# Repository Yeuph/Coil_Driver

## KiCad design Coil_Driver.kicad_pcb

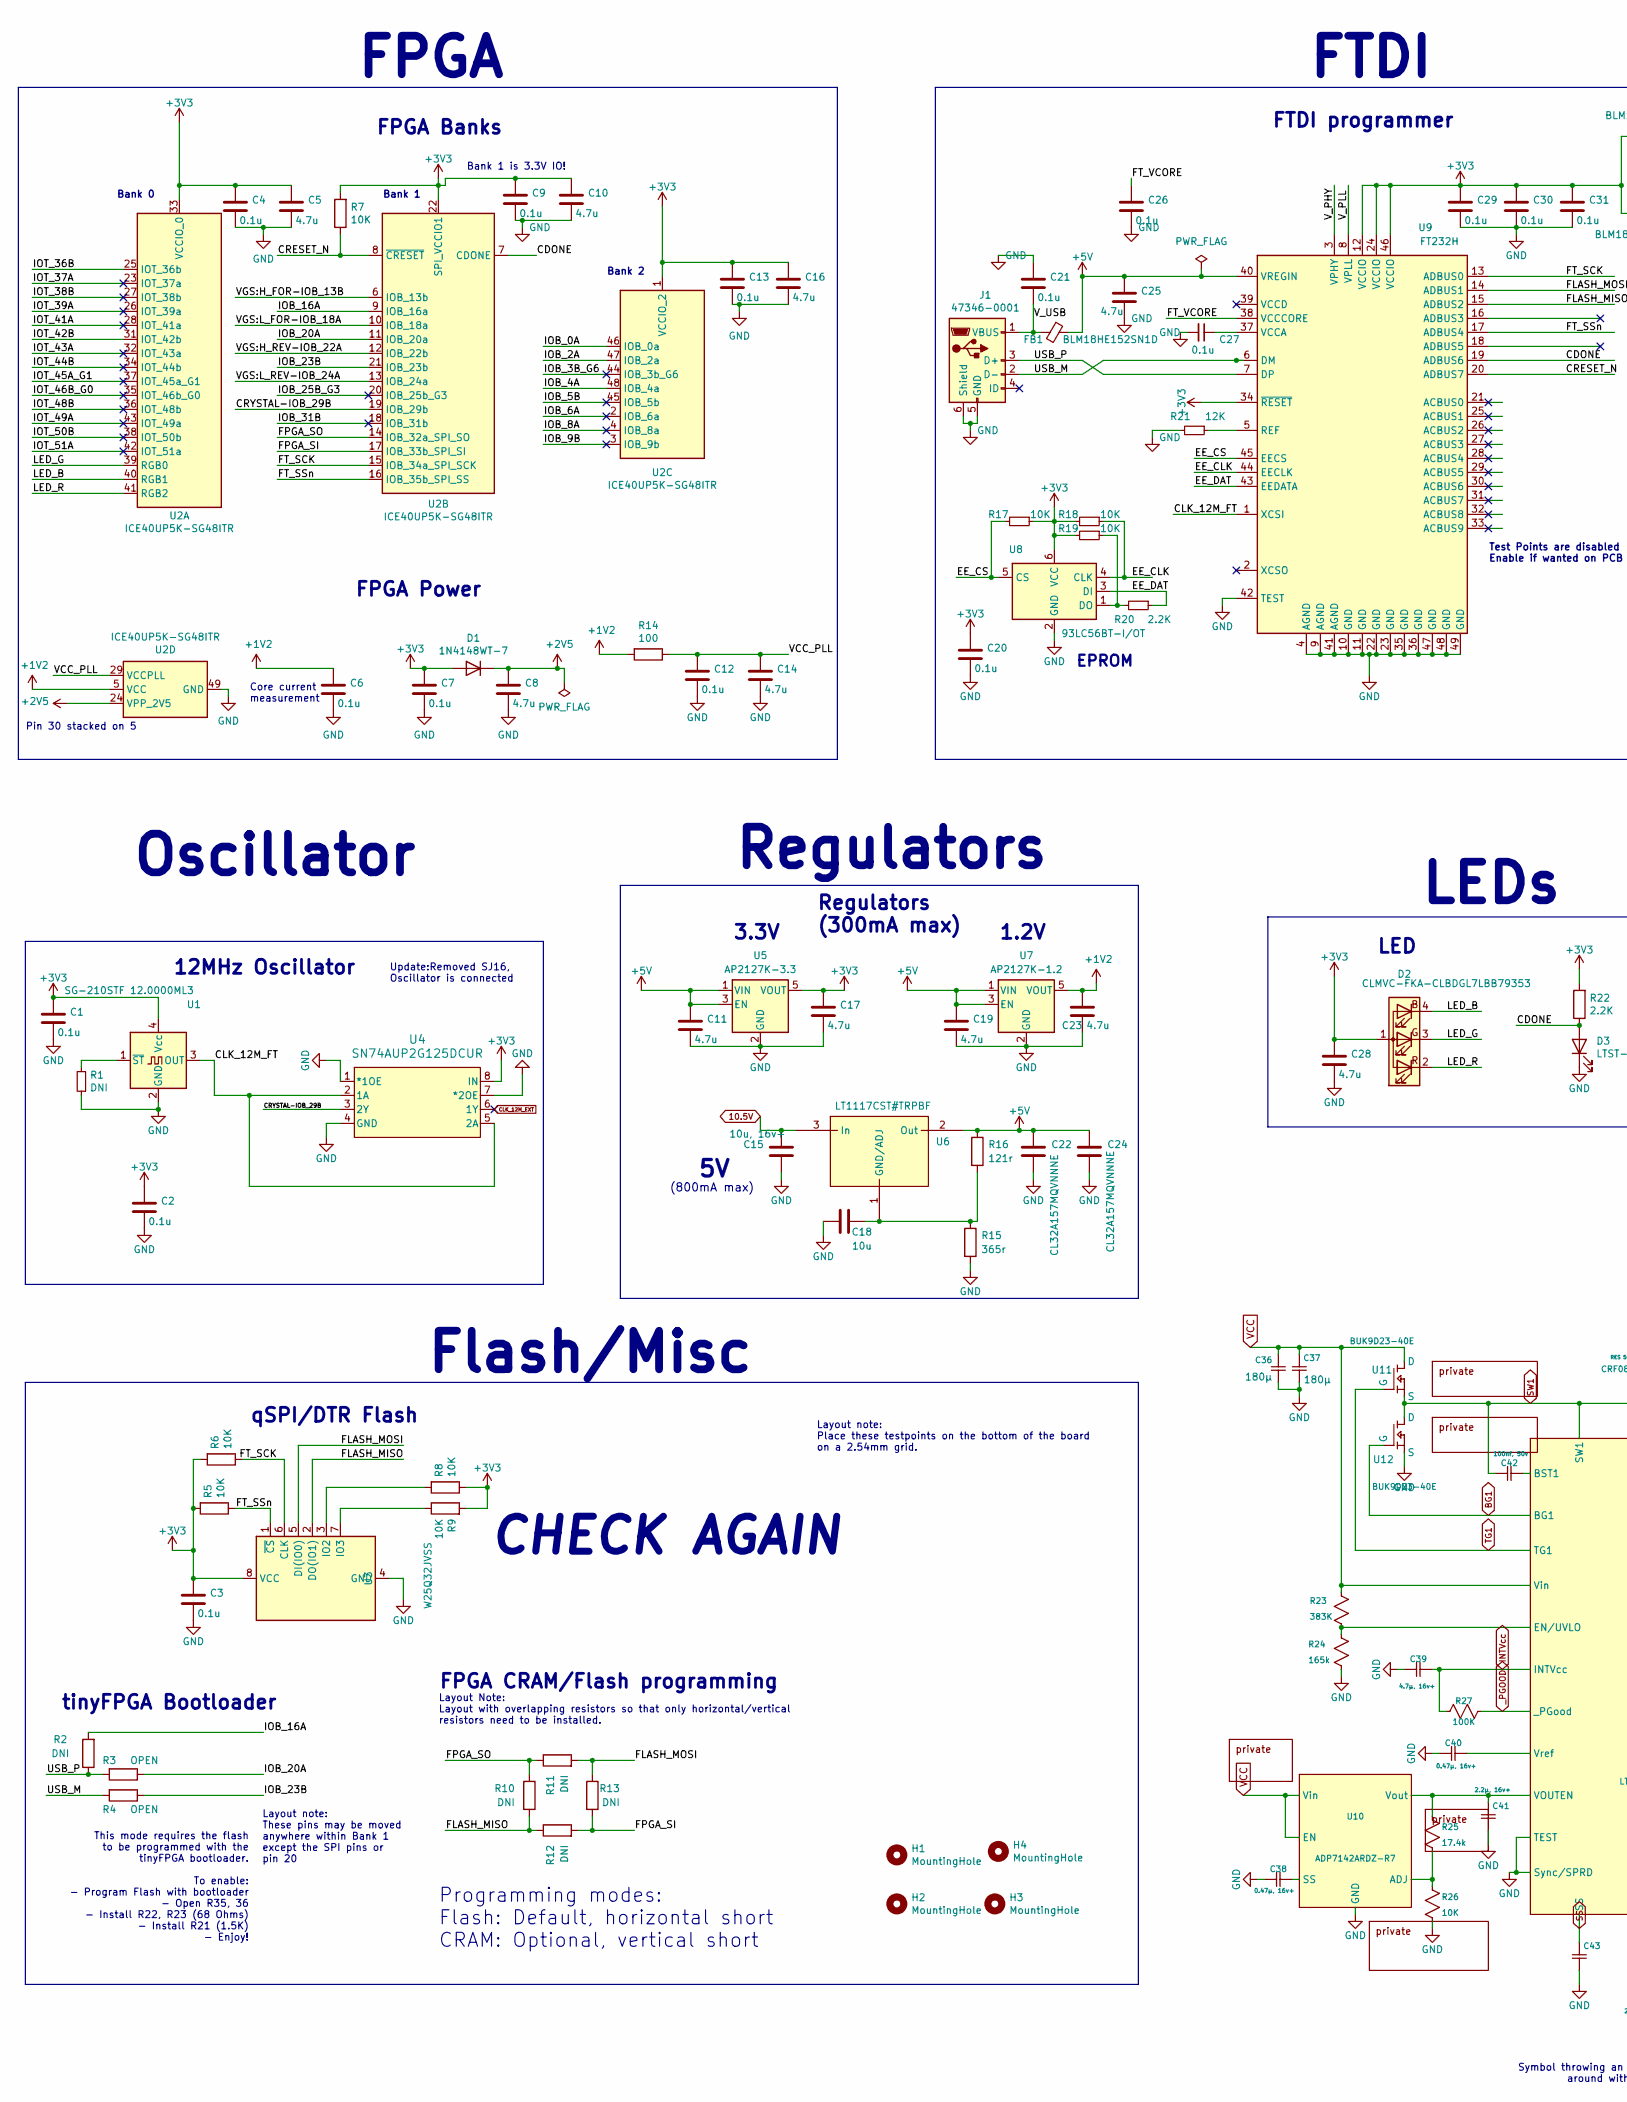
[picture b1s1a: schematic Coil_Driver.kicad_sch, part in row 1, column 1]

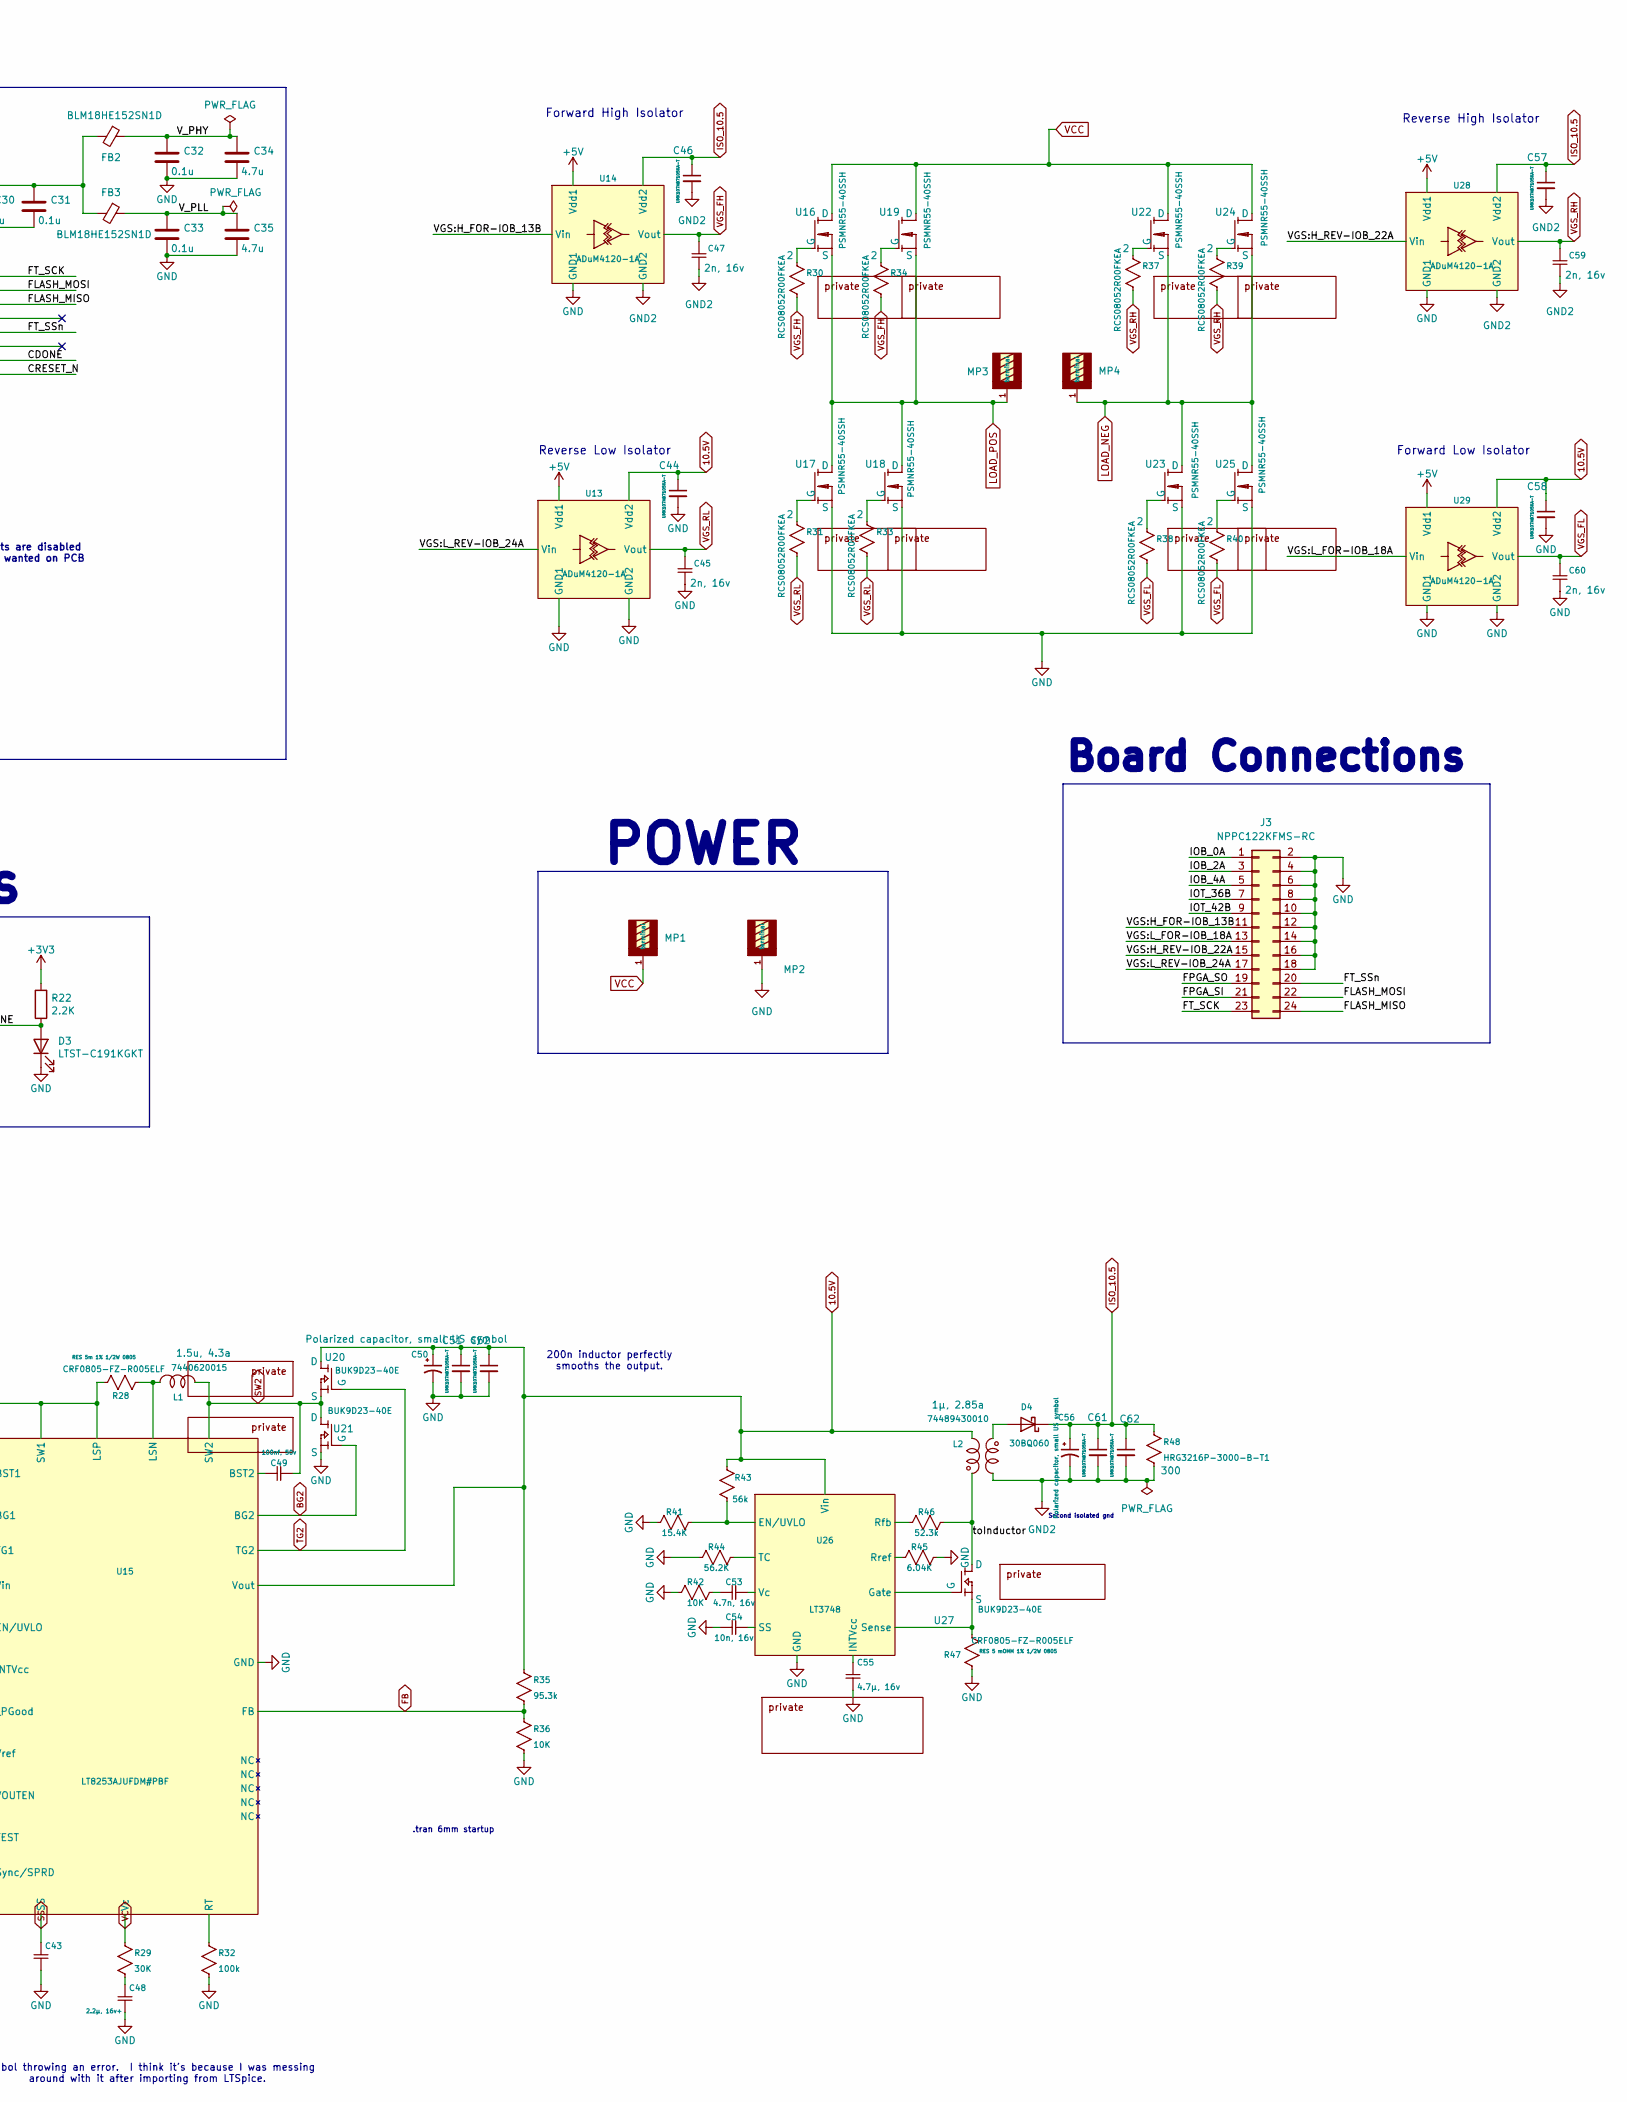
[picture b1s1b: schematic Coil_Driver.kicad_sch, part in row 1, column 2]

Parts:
C1, C2, C3, C6, C7, C9, C12, C13, C20, C21, C26, C27, C29, C30, C31, C32, C33: 0.1u; C_0603_1608Metric
C4: 0.1u; C_0603_1608Metric; MPN C1005X5R0J104K050BA
C5, C8, C10, C11, C14, C16, C17, C19, C23, C25, C28, C34, C35: 4.7u; C_0603_1608Metric
C15: 10u, 16v+; C_0805_2012Metric
C18: 10u; C_0805_2012Metric
C22, C24: CL32A157MQVNNNE; C_1210_3225Metric
C36, C37: PCR1H181MCL1GS
C38, C40: EMK105ABJ474KV-F; C_0402_1005Metric
C39: CL10A475KO8NNNC; C_0603_1608Metric
C41, C48: CL10A225KO8NNNC; C_0603_1608Metric
C42, C49: CL10B104KB8NNNC; C_0603_1608Metric
C43: GRM155R71C103KA01D; C_0603_1608Metric
C44, C46, C51, C52, C57, C58, C61, C62: UMK107AB7105KA-T; C_0603_1608Metric
C45, C47, C59, C60: C0402C202J3GACTU; C_0402_1005Metric
C50, C56: APXG250ARA221MJA0G
C53: 4.7n, 16v; C_0603_1608Metric
C54: 10n, 16v; C_0603_1608Metric
C55: 4.7µ, 16v; C_0603_1608Metric
D1: 1N4148WT-7; D_SOD-123
D2: CLMVC-FKA-CLBDGL7LBB79353; LED_Cree-PLCC4_2x2mm_CW
D3: LTST-C191KGKT; LED_0603_1608Metric
D4: 30BQ060; D_SMC
FB1, FB2, FB3: BLM18HE152SN1D; L_0603_1608Metric
H1, H2, H3, H4: MountingHole; MountingHole_3.2mm_M3
J1: 47346-0001; USB_Micro-B_Molex_47346-0001
J3: NPPC122KFMS-RC; PinHeader_2x12_P2.54mm_Vertical_SMD
L1: 7440620015; WE-TPC_6823
L2: 74489430010; WE-TDC-8018
MP1, MP2, MP3, MP4: 7466205R; PART-NUMBER 7466205R
R1, R2, R10, R11, R12, R13: DNI; R_0603_1608Metric
R3, R4: OPEN; SolderJumper-2_P1.3mm_Open_TrianglePad1.0x1.5mm
R5, R6, R7, R8, R9, R17, R18, R19, R26: 10K; R_0603_1608Metric
R14: 100; R_0603_1608Metric
R15: 365r; R_0603_1608Metric
R16: 121r; R_0603_1608Metric
R20, R22: 2.2K; R_0603_1608Metric
R21: 12K; R_0603_1608Metric
R23: 383K; R_0603_1608Metric
R24: 165k; R_0603_1608Metric
R25: 17.4k; R_0603_1608Metric
R27: 100K; R_0603_1608Metric
R28, R47: CRF0805-FZ-R005ELF; R_0805_2012Metric
R29: 30K; R_0603_1608Metric
R30, R31, R33, R34, R37, R38, R39, R40: RCS08052R00FKEA; R_0805_2012Metric
R32: 100k; R_0603_1608Metric
R35: 95.3k; R_0402_1005Metric
R36, R42: 10K; R_0402_1005Metric
R41: 15.4K; R_0402_1005Metric
R43: 56k; R_0402_1005Metric
R44: 56.2K; R_0402_1005Metric
R45: 6.04K; R_0402_1005Metric
R46: 52.3k; R_0402_1005Metric
R48: HRG3216P-3000-B-T1; R_1206_3216Metric
U1: SG-210STF 12.0000ML3; Oscillator_SMD_SeikoEpson_SG210-4Pin_2.5x2.0mm
U2: ICE40UP5K-SG48ITR; QFN-48-1EP_7x7mm_P0.5mm_EP5.6x5.6mm
U3: W25Q32JVSS; SOIC-8_5.23x5.23mm_P1.27mm
U4: SN74AUP2G125DCUR; VSSOP-8_2.3x2mm_P0.5mm
U5: AP2127K-3.3; SOT-23-5
U6: LT1117CST#TRPBF; SOT-223-3_TabPin2
U7: AP2127K-1.2; SOT-23-5
U8: 93LC56BT-I/OT; SOT-23-6
U9: FT232H; QFN-48-1EP_8x8mm_P0.5mm_EP6.2x6.2mm
U10: ADP7142ARDZ-R7; SOIC-8-1EP_3.9x4.9mm_P1.27mm_EP2.29x3mm
U11, U12, U20, U21, U27: BUK9D23-40E; Diodes_UDFN2020-6_Type-F
U13, U14, U28, U29: ADuM4120-1A; RI_6_1_ADI-M
U15: LT8253AJUFDM#PBF; QFN-28-1EP_4x5mm_P0.5mm_EP2.65x3.65mm
U16, U17, U18, U19, U22, U23, U24, U25: PSMNR55-40SSH; LFPAK88_SOT1235_NEX-M
U26: LT3748; MSOP-12-16_3x4mm_P0.5mm

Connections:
10.5V: C15.1, C44.1, C50.1, C51.1, C52.1, C58.1, L2.2, R35.1, R43.2, U6.3 (In), U13.6 (Vdd2), U15.21 (Vout), U20.1 (D), U20.2 (D), U20.5 (D), U20.6 (D), U20.7 (D), U26.1 (Vin), U29.6 (Vdd2)
+1V2: C6.1, C23.1, R14.2, U2.5 (VCC), U2.30 (VCC), U7.5 (VOUT)
+2V5: C8.1, D1.1 (K), U2.24 (VPP_2V5)
+3V3: C1.1, C2.1, C3.1, C4.1, C5.1, C7.1, C9.1, C10.1, C13.1, C16.1, C17.1, C20.1, C28.1, C29.1, C30.1, C31.1, D1.2 (A), D2.1 (A), FB2.2, FB3.2, R5.2, R6.2, R7.2, R8.1, R9.2, R17.1, R18.2, R19.2, R22.2, U1.4 (Vcc), U2.1 (VCCIO_2), U2.22 (SPI_VCCIO1), U2.33 (VCCIO_0), U3.8 (VCC), U4.8 (IN), U5.5 (VOUT), U8.6 (VCC), U9.12 (VCCIO), U9.24 (VCCIO), U9.34 (~RESET), U9.46 (VCCIO)
+5V: C11.1, C19.1, C22.1, C24.1, C25.1, FB1.1, R16.1, U5.1 (VIN), U5.3 (EN), U6.2 (Out), U7.1 (VIN), U7.3 (EN), U9.40 (VREGIN), U13.1 (Vdd1), U14.1 (Vdd1), U28.1 (Vdd1), U29.1 (Vdd1)
/CDONE: D3.2 (A), R22.1, U2.7 (CDONE), U9.19 (ADBUS6)
/CLK_12M_FT: U1.3 (OUT), U4.2 (1A), U4.5 (2A), U9.1 (XCSI)
/CRESET_N: R7.1, U2.8 (~CRESET), U9.20 (ADBUS7)
/CRYSTAL-IOB_29B: U2.19 (IOB_29b), U4.3 (2Y)
/EE_CLK: R18.1, U8.4 (CLK), U9.44 (EECLK)
/EE_CS: R17.2, U8.5 (CS), U9.45 (EECS)
/EE_DAT: R20.1, U8.3 (DI), U9.43 (EEDATA)
/FLASH_MISO: J3.24, R10.2, R12.1, U3.2 (DO(IO1)), U9.15 (ADBUS2)
/FLASH_MOSI: J3.22, R11.2, R13.1, U3.5 (DI(IO0)), U9.14 (ADBUS1)
/FPGA_SI: J3.21, R12.2, R13.2, U2.17 (IOB_33b_SPI_SI)
/FPGA_SO: J3.19, R10.1, R11.1, U2.14 (IOB_32a_SPI_SO)
/FT_SCK: J3.23, R6.1, U2.15 (IOB_34a_SPI_SCK), U3.6 (CLK), U9.13 (ADBUS0)
/FT_SSn: J3.20, R5.1, U2.16 (IOB_35b_SPI_SS), U3.1 (~CS), U9.17 (ADBUS4)
/FT_VCORE: C26.1, U9.38 (VCCCORE)
/IOB_0A: J3.1, U2.46 (IOB_0a)
/IOB_2A: J3.3, U2.47 (IOB_2a)
/IOB_3B_G6: U2.44 (IOB_3b_G6)
/IOB_4A: J3.5, U2.48 (IOB_4a)
/IOB_5B: U2.45 (IOB_5b)
/IOB_6A: U2.2 (IOB_6a)
/IOB_8A: U2.4 (IOB_8a)
/IOB_9B: U2.3 (IOB_9b)
/IOB_16A: R2.2, U2.9 (IOB_16a)
/IOB_20A: R3.1, U2.11 (IOB_20a)
/IOB_23B: R4.1, U2.21 (IOB_23b)
/IOB_25B_G3: U2.20 (IOB_25b_G3)
/IOB_31B: U2.18 (IOB_31b)
/IOT_36B: J3.7, U2.25 (IOT_36b)
/IOT_37A: U2.23 (IOT_37a)
/IOT_38B: U2.27 (IOT_38b)
/IOT_39A: U2.26 (IOT_39a)
/IOT_41A: U2.28 (IOT_41a)
/IOT_42B: J3.9, U2.31 (IOT_42b)
/IOT_43A: U2.32 (IOT_43a)
/IOT_44B: U2.34 (IOT_44b)
/IOT_45A_G1: U2.37 (IOT_45a_G1)
/IOT_46B_G0: U2.35 (IOT_46b_G0)
/IOT_48B: U2.36 (IOT_48b)
/IOT_49A: U2.43 (IOT_49a)
/IOT_50B: U2.38 (IOT_50b)
/IOT_51A: U2.42 (IOT_51a)
/LED_B: D2.4 (BK), U2.40 (RGB1)
/LED_G: D2.3 (GK), U2.39 (RGB0)
/LED_R: D2.2 (RK), U2.41 (RGB2)
/USB_M: J1.2 (D-), R4.2, U9.6 (DM)
/USB_P: J1.3 (D+), R2.1, R3.2, U9.7 (DP)
/VCC_PLL: C12.1, C14.1, R14.1, U2.29 (VCCPLL)
/VGS:H_FOR-IOB_13B: J3.11, U2.6 (IOB_13b), U14.2 (Vin)
/VGS:H_REV-IOB_22A: J3.15, U2.12 (IOB_22b), U28.2 (Vin)
/VGS:L_FOR-IOB_18A: J3.13, U2.10 (IOB_18a), U29.2 (Vin)
/VGS:L_REV-IOB_24A: J3.17, U2.13 (IOB_24a), U13.2 (Vin)
/V_PHY: C32.1, C34.1, FB2.1, U9.3 (VPHY)
/V_PLL: C33.1, C35.1, FB3.1, U9.8 (VPLL)
/V_USB: C21.2, FB1.2, J1.1 (VBUS)
/toInductor: L2.3, R46.1, U27.1 (D), U27.2 (D), U27.5 (D), U27.6 (D), U27.7 (D)
BG1: U12.3 (G), U15.26 (BG1)
BG2: U15.25 (BG2), U21.3 (G)
CLK_12M_EXT: U4.6 (1Y)
FB: R35.2, R36.1, U15.16 (FB)
GND: C1.2, C2.2, C3.2, C4.2, C5.2, C6.2, C7.2, C8.2, C9.2, C10.2, C11.2, C12.2, C13.2, C14.2, C15.2, C16.2, C17.2, C18.1, C19.2, C20.2, C21.1, C22.2, C23.2, C24.2, C25.2, C26.2, C27.2, C28.2, C29.2, C30.2, C31.2, C32.2, C33.2, C34.2, C35.2, C36.2, C37.2, C38.2, C39.2, C40.2, C41.2, C43.2, C44.2, C45.2, C48.2, C50.2, C51.2, C52.2, C54.2, C55.1, C58.2, C60.2, D3.1 (K), J1.5 (GND), J1.6 (Shield), J3.2, J3.4, J3.6, J3.8, J3.10, J3.12, J3.14, J3.16, J3.18, MP2.1 (terminal), R1.1, R15.2, R21.2, R24.2, R26.2, R32.2, R36.2, R41.2, R42.2, R44.2, R45.2, R47.1, U1.2 (GND), U2.49 (GND), U3.4 (GND), U4.1 (*1OE), U4.4 (GND), U4.7 (*2OE), U5.2 (GND), U7.2 (GND), U8.2 (GND), U9.4 (AGND), U9.9 (AGND), U9.10 (GND), U9.11 (GND), U9.22 (GND), U9.23 (GND), U9.35 (GND), U9.36 (GND), U9.41 (AGND), U9.42 (TEST), U9.47 (GND), U9.48 (GND), U9.49 (GND), U10.4 (GND), U10.9 (GND), U12.4 (S), U12.8 (S), U13.3 (GND1), U13.4 (GND2), U14.3 (GND1), U15.7 (TEST), U15.19 (Sync/SPRD), U15.29 (GND), U17.2 (S), U17.3 (S), U17.4 (S), U18.2 (S), U18.3 (S), U18.4 (S), U21.4 (S), U21.8 (S), U23.2 (S), U23.3 (S), U23.4 (S), U25.2 (S), U25.3 (S), U25.4 (S), U26.8 (GND), U26.9 (GND), U28.3 (GND1), U29.3 (GND1), U29.4 (GND2)
GND2: C46.2, C47.2, C56.2, C57.2, C59.2, C61.2, C62.2, L2.1, R48.2, U14.4 (GND2), U28.4 (GND2)
INTVcc: C39.1, R27.2, U15.5 (INTVcc)
ISO_10.5: C46.1, C56.1, C57.1, C61.1, C62.1, D4.1 (K), R48.1, U14.6 (Vdd2), U28.6 (Vdd2)
LOAD_NEG: MP4.1 (terminal), U22.2 (S), U22.3 (S), U22.4 (S), U23.5 (D), U24.2 (S), U24.3 (S), U24.4 (S), U25.5 (D)
LOAD_POS: MP3.1 (terminal), U16.2 (S), U16.3 (S), U16.4 (S), U17.5 (D), U18.5 (D), U19.2 (S), U19.3 (S), U19.4 (S)
unnamed: C48.1, R29.2
unnamed: C53.2, R42.1
unnamed: D4.2 (A), L2.4
unnamed: R1.2, U1.1 (~ST)
unnamed: R8.2, U3.3 (IO2)
unnamed: R9.1, U3.7 (IO3)
unnamed: C18.2, R15.1, R16.2, U6.1 (GND/ADJ)
unnamed: R19.1, R20.2, U8.1 (DO)
unnamed: R21.1, U9.5 (REF)
unnamed: C27.1, U9.37 (VCCA)
unnamed: R25.2, R26.1, U10.3 (ADJ)
unnamed: C38.1, U10.6 (SS)
unnamed: C42.1, U15.27 (BST1)
unnamed: C49.2, U15.24 (BST2)
unnamed: R23.2, R24.1, U15.6 (EN/UVLO)
unnamed: L1.1, R28.2, U15.3 (LSN)
unnamed: R32.1, U15.18 (RT)
unnamed: C41.1, R25.1, U10.1 (Vout), U10.2 (Vout), U15.8 (VOUTEN)
unnamed: C40.1, U15.9 (Vref)
unnamed: R30.1, U16.1 (G)
unnamed: R31.1, U17.1 (G)
unnamed: R33.1, U18.1 (G)
unnamed: R34.1, U19.1 (G)
unnamed: R37.1, U22.1 (G)
unnamed: R38.1, U23.1 (G)
unnamed: R39.1, U24.1 (G)
unnamed: R40.1, U25.1 (G)
unnamed: R41.1, R43.1, U26.3 (EN/UVLO)
unnamed: U26.6 (Gate), U27.3 (G)
unnamed: C55.2, U26.5 (INTVcc)
unnamed: R46.2, U26.16 (Rfb)
unnamed: R45.1, U26.14 (Rref)
unnamed: C54.1, U26.10 (SS)
unnamed: R47.2, U26.7 (Sense), U27.4 (S), U27.8 (S)
unnamed: R44.1, U26.12 (TC)
unnamed: C53.1, U26.11 (Vc)
SS: C43.1, U15.15 (SS)
SW1: C42.2, R28.1, U11.4 (S), U11.8 (S), U12.1 (D), U12.2 (D), U12.5 (D), U12.6 (D), U12.7 (D), U15.2 (LSP), U15.28 (SW1)
SW2: C49.1, L1.2, U15.23 (SW2), U20.4 (S), U20.8 (S), U21.1 (D), U21.2 (D), U21.5 (D), U21.6 (D), U21.7 (D)
TG1: U11.3 (G), U15.1 (TG1)
TG2: U15.22 (TG2), U20.3 (G)
VC: R29.1, U15.17 (Vc)
VCC: C36.1, C37.1, MP1.1 (terminal), R23.1, U10.5 (EN), U10.7 (Vin), U10.8 (Vin), U11.1 (D), U11.2 (D), U11.5 (D), U11.6 (D), U11.7 (D), U15.4 (Vin), U16.5 (D), U19.5 (D), U22.5 (D), U24.5 (D)
VGS_FH: C47.1, R30.2, R34.2, U14.5 (Vout)
VGS_FL: C60.1, R38.2, R40.2, U29.5 (Vout)
VGS_RH: C59.1, R37.2, R39.2, U28.5 (Vout)
VGS_RL: C45.1, R31.2, R33.2, U13.5 (Vout)
_PGOOD: R27.1, U15.14 (_PGood)

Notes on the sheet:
Layout note: These pins may be moved anywhere within Bank 1 except the SPI pins or pin 20
LEDs
Flash/Misc
Reverse Low Isolator
Bank 2
200n inductor perfectly smooths the output.
Forward Low Isolator
Bank 1 is 3.3V IO!
Layout note: Place these testpoints on the bottom of the board on a 2.54mm grid.
Second isolated gnd
1.2V
Update:Removed SJ16, Oscillator is connected
POWER
Regulators (300mA max)
FPGA Banks
Pin 30 stacked on 5
Bank 0
This mode requires the flash to be programmed with the tinyFPGA bootloader. To enable: - Program Flash with bootloader - Open R35, 36 - Install R22, R23 (68 Ohms) - Install R21 (1.5K) - Enjoy!
Board Connections
CHECK AGAIN
FTDI
Regulators
EPROM
Core current measurement
LED
FTDI programmer
qSPI/DTR Flash
(800mA max)
tinyFPGA Bootloader
FPGA CRAM/Flash programming
12MHz Oscillator
Layout Note: Layout with overlapping resistors so that only horizontal/vertical resistors need to be installed.
Symbol throwing an error. I think it's because I was messing around with it after importing from LTSpice.
FPGA Power
Oscillator
.tran 6mm startup
3.3V
Reverse High Isolator
Test Points are disabled Enable if wanted on PCB
Forward High Isolator

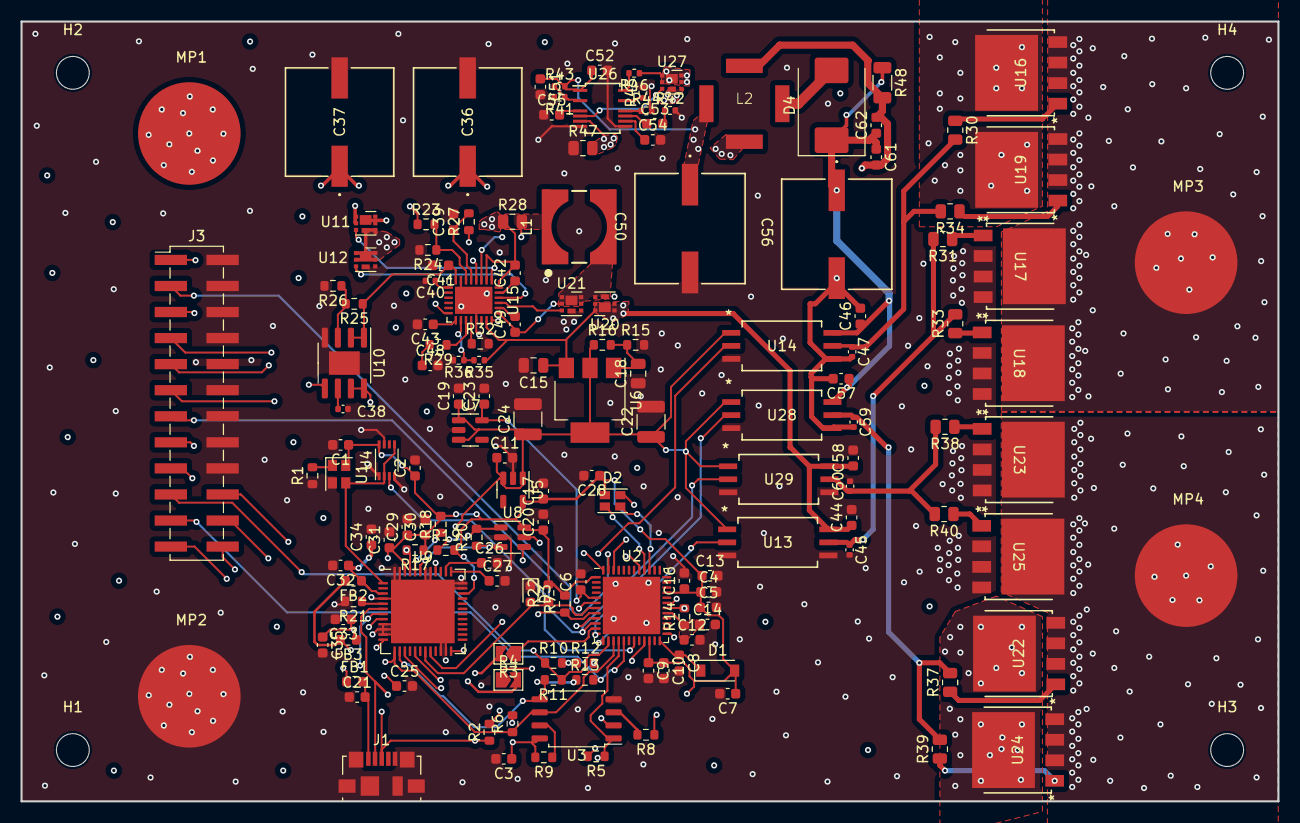
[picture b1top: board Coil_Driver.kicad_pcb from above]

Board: 8 copper layers, 122.5 x 76.0 mm, 158 parts (0 on the bottom side), 98 nets.

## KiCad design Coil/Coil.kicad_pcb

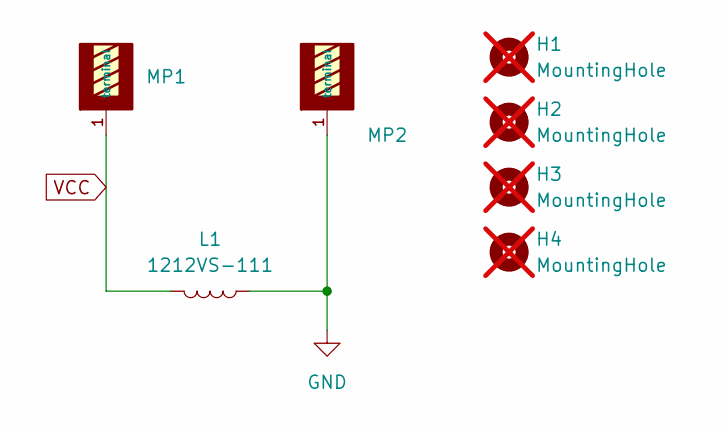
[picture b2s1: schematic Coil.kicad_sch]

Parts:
H1, H2, H3, H4: MountingHole; MountingHole_3.2mm_M3; not fitted
L1: 1212VS-111; 1212VS
MP1, MP2: 7466205R; PART-NUMBER 7466205R

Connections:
GND: L1.1, MP2.1 (terminal)
VCC: L1.2, MP1.1 (terminal)

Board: 2 copper layers, 7 parts (2 on the bottom side), 2 nets, no tracks yet.

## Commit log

2025-01-30 prototype high current ice40 controlled h bridge
2025-01-30 Added verilog control files
2025-02-01 Changed R28 to the correct value and part
2025-02-02 Changed R47 to correct value
2025-02-02 Rotated L2 90° clockwise
2025-02-03 Fixed L2 symbol and PCB orientation
2025-02-09 Changed via annular rings to connections only. Required change to zone priority on toplayer U26-Sense pour. Layers 5 and 6 extended past mosfets into terminal planes. Changed zone priorites to fix. C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
